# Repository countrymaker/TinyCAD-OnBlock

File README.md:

# TinyCAD-OnBlock for Windows

TinyCAD-OnBlock is schematic capture for the additional purpose of using TinyCAD as a Function Block Editor.  
TinyCAD-OnBlock = TinyCAD 3.00.04 + KiCad Netlist + Arduino(C++) Code Composer + FB Library  

## License
This program keeps on GNU LGPL.  

## Modifications
Some TinyCAD sources are modified and 2 files(OnBlock.h, OnBlock.cpp) are added in src by countrymaker.  
The modified lines of source files are marked with "// cmaker".  

## Examples

### Function Block Capture

### Composed Arduino Source Code (.ino)

___

# TinyCAD for Windows

TinyCAD is an open source circuit capture program.  The offical web-site is [www.tinycad.net](https://www.tinycad.net)

## Binaries

If you want to install TinyCAD then go to the [Downloads](https://www.tinycad.net/Home/Download) page.

## Building from source

Help on building TinyCAD from source is available in the [Wiki](https://github.com/matt123p/TinyCAD/wiki/How-to-build-TinyCAD)

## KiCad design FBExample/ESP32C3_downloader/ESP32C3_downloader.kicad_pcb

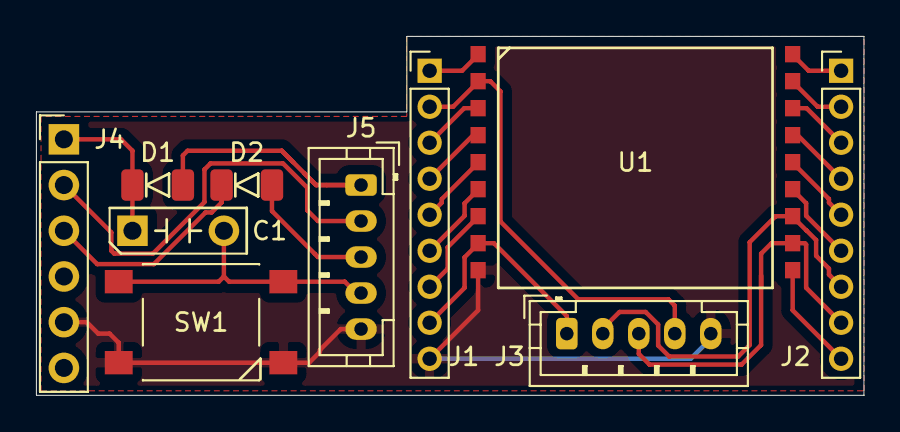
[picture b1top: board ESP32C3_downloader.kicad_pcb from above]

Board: 2 copper layers, 46.0 x 19.9 mm, 10 parts (0 on the bottom side), 24 nets.

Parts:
C1: 105; FP_TH200mil
D1, D2: 1N4148; FP_DS_SM3216
J1, J2: Header9_2.0mm; FP_Header9_2.0mm
J3, J5: JST_PH5_2.0mm; FP_JST_PH5_2.0mm
J4: Header6; FP_Header6
SW1: SW Push Button; FP_TactSW_SM6.0mm
U1: ESP-C3-13; FP_ESP-C3-13

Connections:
GND: J1.9, J3.5, J4.5, J5.5, SW1.1, U1.9
_N_2: J2.8, J3.3, U1.11
_N_3: J2.7, J3.2, U1.12
_N_4: J2.6, U1.13
_N_5: J2.5, U1.14
_N_6: J2.4, U1.15
_N_7: J2.3, U1.16
_N_8: J2.2, U1.17
_N_9: J2.1, U1.18
_N_10: J2.9, U1.10
_N_11: J1.1, U1.1
_N_12: J1.2, J3.4, U1.2
_N_13: J1.3, U1.3
_N_14: J1.4, U1.4
_N_15: J1.5, U1.5
_N_16: J1.6, U1.6
_N_17: J1.7, U1.7
_N_18: J1.8, J3.1, U1.8
_N_19: D1.2, J5.1
_N_20: D2.2, J5.3
_N_21: D2.1, J4.3
_N_22: J4.2, J5.2
_N_23: C1.2, J5.4, SW1.2
_N_24: C1.1, D1.1, J4.1

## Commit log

2021-12-02 init
2021-12-02 2021-12-02 22:18
2021-12-02 Second commit
2021-12-03 2021-12-03 20:57
2021-12-03 2021-12-03 21:50
2021-12-03 2021-12-04 07:21
2021-12-06 2021-12-07
